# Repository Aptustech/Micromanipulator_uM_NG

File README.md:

# Micromanipulator_uM_NG

> ⚠️ **Disclaimer:** This is a preliminary hardware design and is currently **untested**. Use or produce these designs at your own risk.

**Micromanipulator_uM_NG** is a next-generation controller system designed for precision micromanipulation. It improves upon previous designs by introducing higher processing power, expanded I/O capabilities, reliable high-speed sensor communication, and comprehensive power monitoring.

## Acknowledgments & Prior Work

This project is the next-generation iteration of the original electronic system for [MicroManipulatorStepper](https://github.com/0x23/MicroManipulatorStepper) by [@0x23](https://github.com/0x23).
---

## Interactive KiCAD Design Viewers

You can inspect the schematics and PCB layouts directly in your browser without opening KiCAD, powered by [KiCanvas](https://kicanvas.org/):

* 🔗 **[View Sensor Board (MT6835 V1.0)](https://kicanvas.org/?repo=https%3A%2F%2Fgithub.com%2FAptustech%2FMicromanipulator_uM_NG%2Ftree%2Fmain%2FMT6835%2FV1.0%2FMT6835)**
* 🔗 **[View Controller Board (uM_Controller V1.0)](https://kicanvas.org/?repo=https%3A%2F%2Fgithub.com%2FAptustech%2FMicromanipulator_uM_NG%2Ftree%2Fmain%2FuM_Controller%2FV1.0%2FuM_Controller)**

---

## Key Features & Highlights

* **Powered by RP2350B:** Upgraded to the RP2350B microcontroller to leverage its high IO count and advanced processing capabilities.
* **High-Speed LVDS Link:** Uses Low-Voltage Differential Signaling (LVDS) lines between the main controller and sensor boards, enabling a high-speed, noise-resilient SPI bus operating at **15 MHz**.
* **Power & Diagnostics:**
  * **Input Voltage Monitoring:** Real-time tracking of the main supply voltage.
  * **Per-Motor Current Sensing:** Dedicated current monitoring for each individual motor driver channel.
* **Modular Expansion:** Includes an dedicated extension connector for easily adding custom interfaces, daughterboards, or peripheral modules.

---

## Hardware Repository Structure

```text
├── MT6835/
│   └── V1.0/          # MT6835 encoder/sensor board design files
└── uM_Controller/
    └── V1.0/          # Main RP2350B controller board design files

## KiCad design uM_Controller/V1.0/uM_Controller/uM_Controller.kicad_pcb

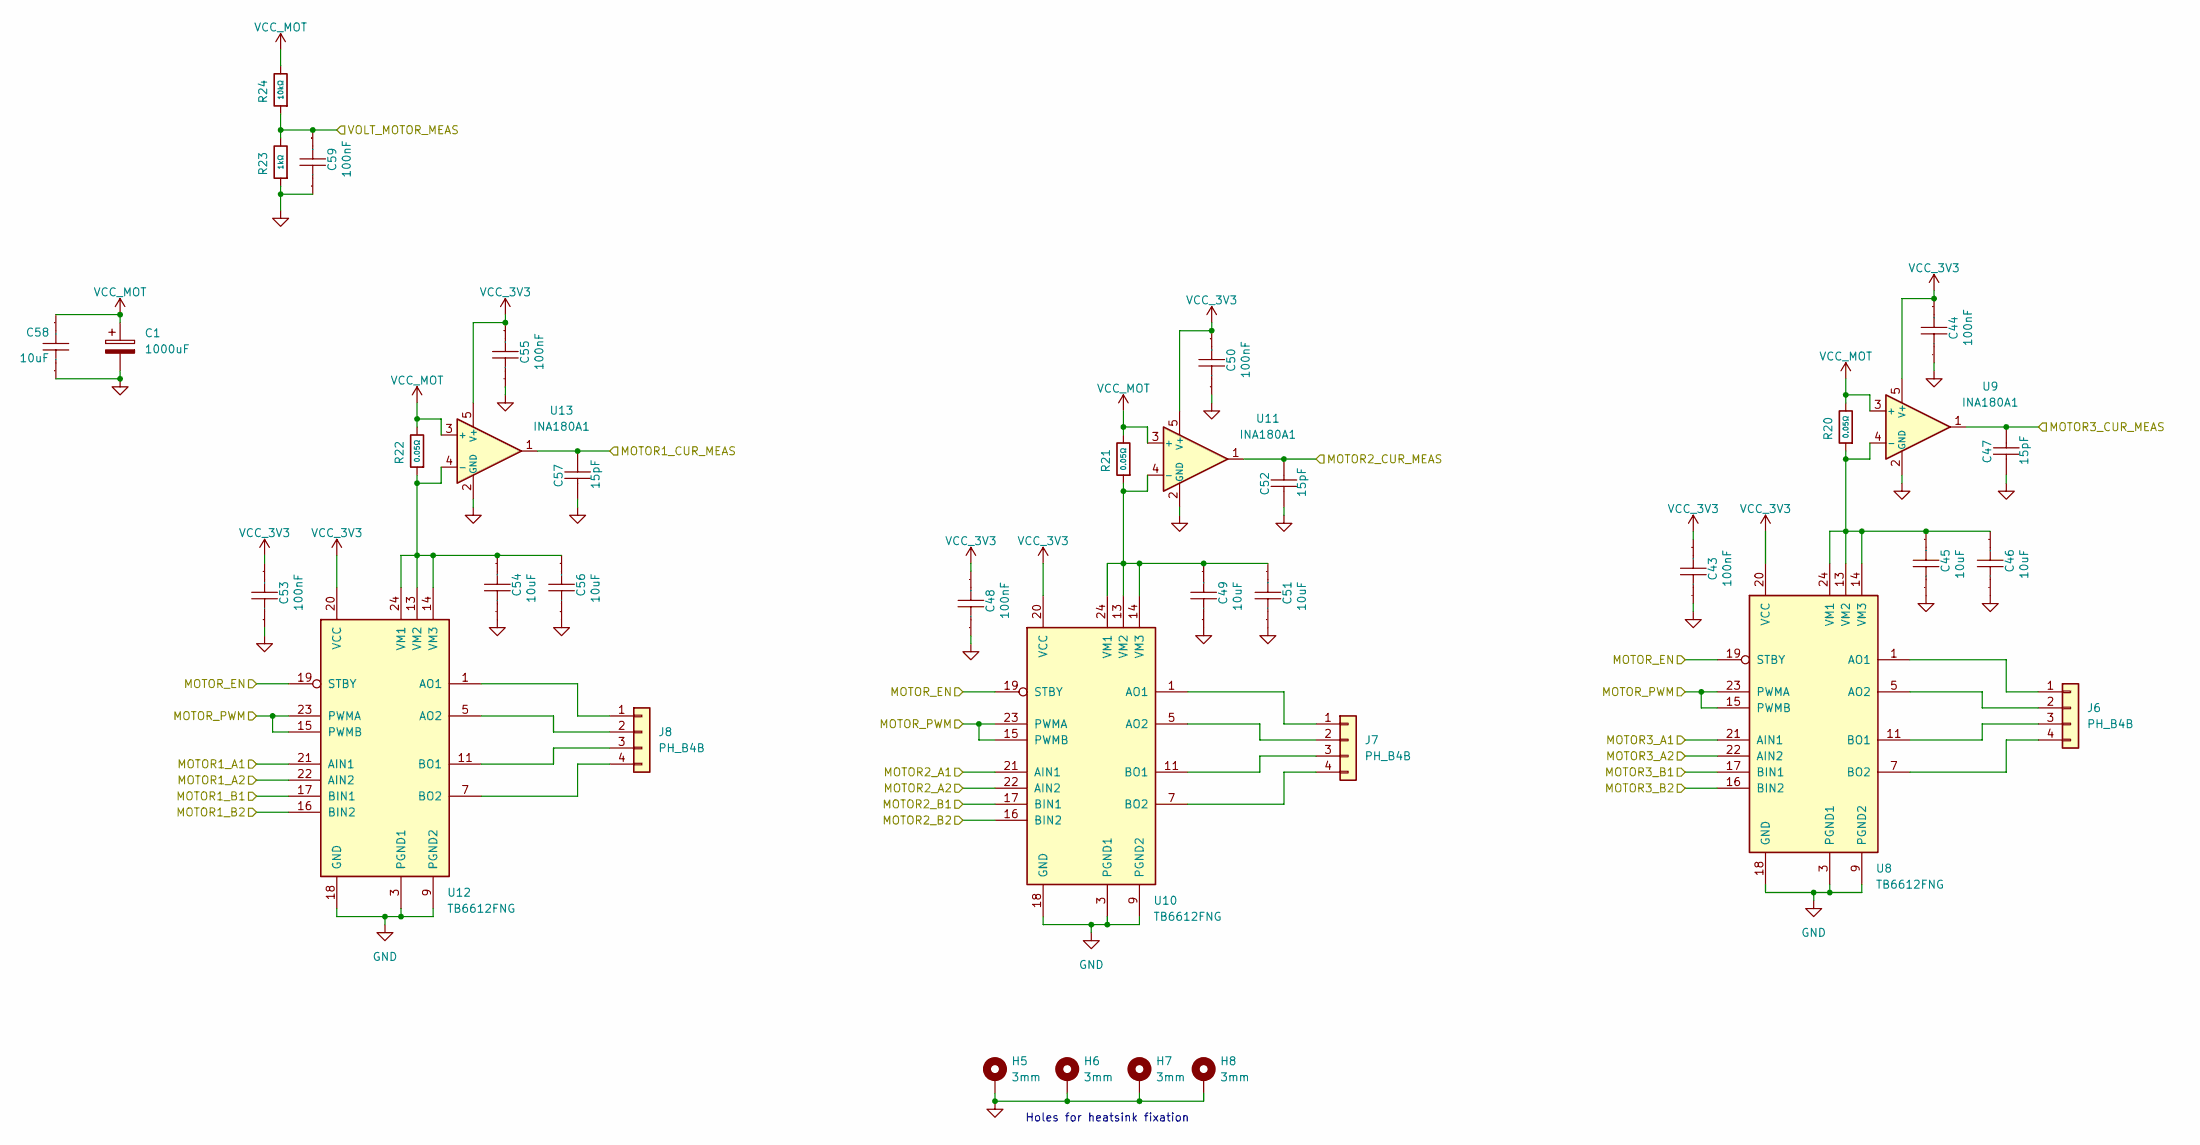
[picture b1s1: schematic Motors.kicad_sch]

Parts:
C1: 1000uF; CP_Radial_D10.0mm_P5.00mm_P7.50mm; Manufacturer Part 16ZLH1000MEFC10X16; LCSC C338175
C43, C44, C48, C50, C53, C55, C59: 100nF; C_0402_1005Metric; Manufacturer Part CL05B104KO5NNNC; LCSC Part Name 100nF ±10% 16V
C45, C46, C49, C51, C54, C56, C58: 10uF; C_1206_3216Metric; Manufacturer Part CL31A106KBHNNNE; LCSC Part Name 10uF ±10% 50V 1206
C47, C52, C57: 15pF; C_0402_1005Metric; Manufacturer Part 0402CG150J500NT; LCSC Part Name 15pF ±5% 50V
H5, H6, H7, H8: 3mm; MountingHole_3.2mm_M3_ISO14580_Pad_TopBottom
J6, J7, J8: PH_B4B; JST_PH_B4B-PH-K_1x04_P2.00mm_Vertical; Manufacturer Part PH-4A; LCSC C2321
R20, R21, R22: 0.05Ω; R_0805_2012Metric; Overload Voltage (Max) 50V; Tolerance ±1%; Part ERJ-6BWFR050V; LCSC C2075868
R23: 1kΩ; R_0402_1005Metric; Overload Voltage (Max) 50V; Tolerance ±1%; Part 0402WGF1001TCE; LCSC C11702
R24: 10kΩ; R_0402_1005Metric; Overload Voltage (Max) 50V; Tolerance ±1%; Part 0402WGF1002TCE; LCSC C25744
U8, U10, U12: TB6612FNG; SSOP-24_5.3x8.2mm_P0.65mm
U9, U11, U13: INA180A1; SOT-23-5

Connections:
/Motors/MOTOR1_A1: U12.21 (AIN1); also elsewhere on the board
/Motors/MOTOR1_A2: U12.22 (AIN2); also elsewhere on the board
/Motors/MOTOR1_B1: U12.17 (BIN1); also elsewhere on the board
/Motors/MOTOR1_B2: U12.16 (BIN2); also elsewhere on the board
/Motors/MOTOR1_CUR_MEAS: C57.1, U13.1; also elsewhere on the board
/Motors/MOTOR2_A1: U10.21 (AIN1); also elsewhere on the board
/Motors/MOTOR2_A2: U10.22 (AIN2); also elsewhere on the board
/Motors/MOTOR2_B1: U10.17 (BIN1); also elsewhere on the board
/Motors/MOTOR2_B2: U10.16 (BIN2); also elsewhere on the board
/Motors/MOTOR2_CUR_MEAS: C52.1, U11.1; also elsewhere on the board
/Motors/MOTOR3_A1: U8.21 (AIN1); also elsewhere on the board
/Motors/MOTOR3_A2: U8.22 (AIN2); also elsewhere on the board
/Motors/MOTOR3_B1: U8.17 (BIN1); also elsewhere on the board
/Motors/MOTOR3_B2: U8.16 (BIN2); also elsewhere on the board
/Motors/MOTOR3_CUR_MEAS: C47.1, U9.1; also elsewhere on the board
/Motors/MOTOR_EN: U8.19 (STBY), U10.19 (STBY), U12.19 (STBY); also elsewhere on the board
/Motors/MOTOR_PWM: U8.15 (PWMB), U8.23 (PWMA), U10.15 (PWMB), U10.23 (PWMA), U12.15 (PWMB), U12.23 (PWMA); also elsewhere on the board
/Motors/VOLT_MOTOR_MEAS: C59.1, R23.2, R24.1; also elsewhere on the board
GND: C1.2, C43.2, C44.2, C45.2, C46.2, C47.2, C48.2, C49.2, C50.2, C51.2, C52.2, C53.2, C54.2, C55.2, C56.2, C57.2, C58.2, C59.2, H5.1 (1_1), H6.1 (1_1), H7.1 (1_1), H8.1 (1_1), R23.1, U8.3 (PGND1), U8.4 (PGND1), U8.9 (PGND2), U8.10 (PGND2), U8.18 (GND), U9.2 (GND), U10.3 (PGND1), U10.4 (PGND1), U10.9 (PGND2), U10.10 (PGND2), U10.18 (GND), U11.2 (GND), U12.3 (PGND1), U12.4 (PGND1), U12.9 (PGND2), U12.10 (PGND2), U12.18 (GND), U13.2 (GND); also elsewhere on the board
unnamed: J6.1, U8.1 (AO1), U8.2 (AO1)
unnamed: J6.2, U8.5 (AO2), U8.6 (AO2)
unnamed: J6.3, U8.11 (BO1), U8.12 (BO1)
unnamed: J6.4, U8.7 (BO2), U8.8 (BO2)
unnamed: J7.1, U10.1 (AO1), U10.2 (AO1)
unnamed: J7.2, U10.5 (AO2), U10.6 (AO2)
unnamed: J7.3, U10.11 (BO1), U10.12 (BO1)
unnamed: J7.4, U10.7 (BO2), U10.8 (BO2)
unnamed: J8.1, U12.1 (AO1), U12.2 (AO1)
unnamed: J8.2, U12.5 (AO2), U12.6 (AO2)
unnamed: J8.3, U12.11 (BO1), U12.12 (BO1)
unnamed: J8.4, U12.7 (BO2), U12.8 (BO2)
unnamed: C45.1, C46.1, R20.1, U8.13 (VM2), U8.14 (VM3), U8.24 (VM1), U9.4 (-)
unnamed: C49.1, C51.1, R21.1, U10.13 (VM2), U10.14 (VM3), U10.24 (VM1), U11.4 (-)
unnamed: C54.1, C56.1, R22.1, U12.13 (VM2), U12.14 (VM3), U12.24 (VM1), U13.4 (-)
VCC_3V3: C43.1, C44.1, C48.1, C50.1, C53.1, C55.1, U8.20 (VCC), U9.5 (V+), U10.20 (VCC), U11.5 (V+), U12.20 (VCC), U13.5 (V+); also elsewhere on the board
VCC_MOT: C1.1, C58.1, R20.2, R21.2, R22.2, R24.2, U9.3 (+), U11.3 (+), U13.3 (+); also elsewhere on the board

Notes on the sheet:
Holes for heatsink fixation

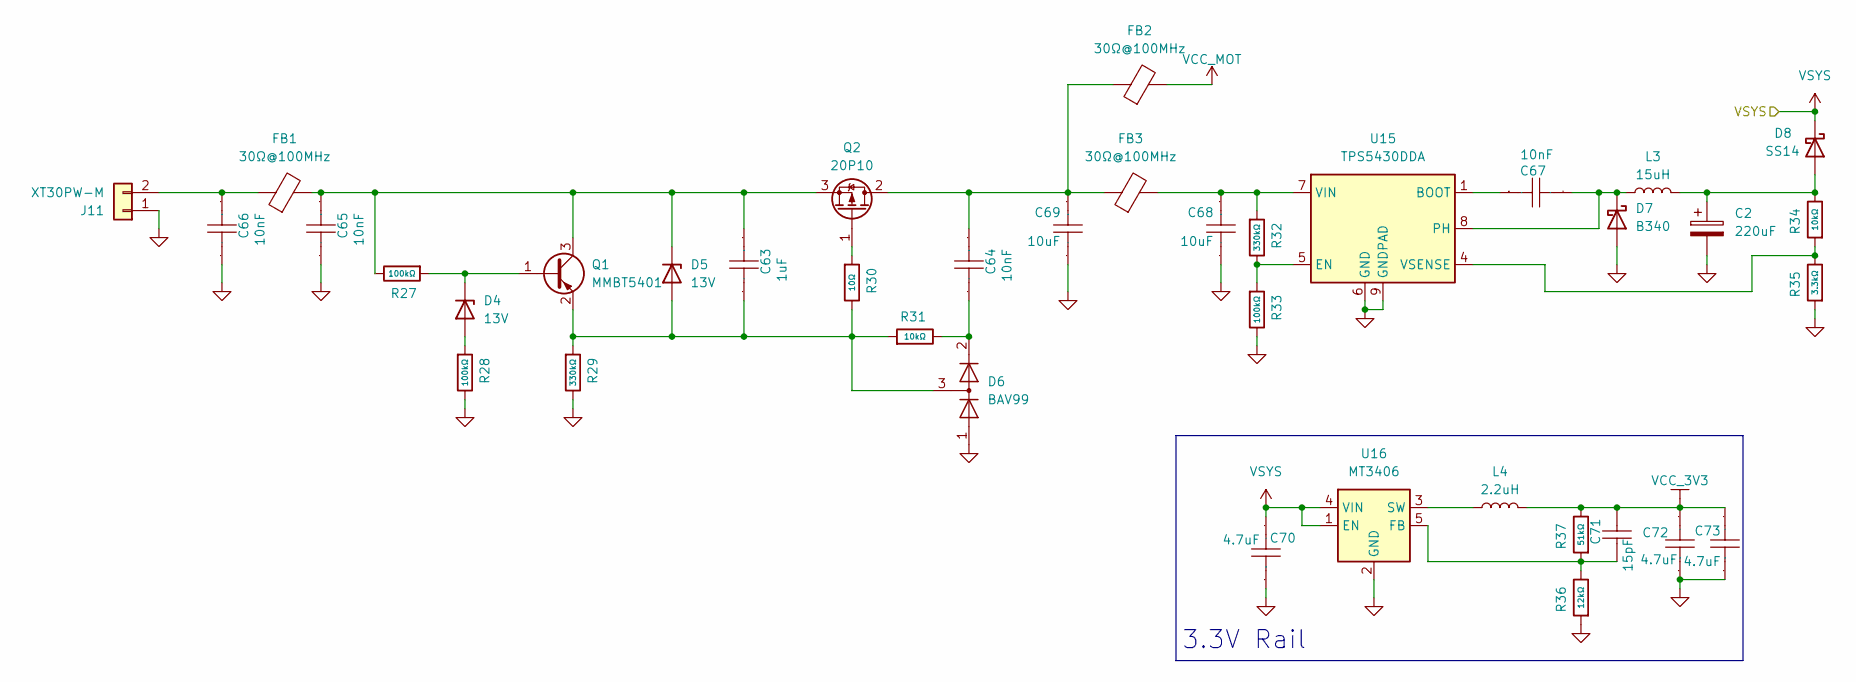
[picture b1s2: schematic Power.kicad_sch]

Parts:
C2: 220uF; CP_Radial_D6.3mm_P2.50mm; Manufacturer Part ERR1AM221E07OT; LCSC C105293
C63: 1uF; C_0603_1608Metric; Manufacturer Part CL10A105KB8NNNC; LCSC C15849
C64, C65, C66, C67: 10nF; C_0603_1608Metric; Manufacturer Part 0603B103K500NT; LCSC C57112
C68, C69: 10uF; C_1206_3216Metric; Manufacturer Part CL31A106KBHNNNE; LCSC Part Name 10uF ±10% 50V 1206
C70, C72, C73: 4.7uF; C_0402_1005Metric; Manufacturer Part CL05A475MP5NRNC; LCSC Part Name 4.7uF ±20% 10V
C71: 15pF; C_0402_1005Metric; Manufacturer Part 0402CG150J500NT; LCSC Part Name 15pF ±5% 50V
D4, D5: 13V; D_SOD-123; Manufacturer Part BZT52C13; LCSC BZT52C13
D6: BAV99; SOT-23; Manufacturer Part BAV99,215; LCSC C2500
D7: B340; D_SMC; Manufacturer Part B340-13-F-HXY; LCSC C52988714
D8: SS14; D_SMA; Manufacturer Part SS14; LCSC C2480
FB1, FB2, FB3: 30Ω@100MHz; L_0805_2012Metric; Manufacturer Part YI201209A300-10R0T; LCSC C20416195
J11: XT30PW-M; AMASS_XT30PW-M_1x02_P2.50mm_Horizontal
L3: 15uH; L_Taiyo-Yuden_NR-60xx; Manufacturer Part FNR6045S150MT; LCSC C168078
L4: 2.2uH; L_1008_2520Metric; Manufacturer Part FTC252010S2R2MBCA; LCSC C5832358
Q1: MMBT5401; SOT-23; Manufacturer Part MMBT5401(RANGE:200-300); LCSC C8326
Q2: 20P10; TO-252-2; Manufacturer Part 20P10; LCSC C18164396
R27, R28, R33: 100kΩ; R_0603_1608Metric; Overload Voltage (Max) 75V; Tolerance ±1%; Part 0603WAF1003T5E; LCSC C25803
R29, R32: 330kΩ; R_0603_1608Metric; Overload Voltage (Max) 75V; Tolerance ±1%; Part 0603WAF3303T5E; LCSC C23137
R30: 10Ω; R_0603_1608Metric; Overload Voltage (Max) 75V; Tolerance ±1%; Part 0603WAF100JT5E; LCSC C22859
R31: 10kΩ; R_0603_1608Metric; Overload Voltage (Max) 75V; Tolerance ±1%; Part 0603WAF1002T5E; LCSC C25804
R34: 10kΩ; R_0402_1005Metric; Overload Voltage (Max) 50V; Tolerance ±1%; Part 0402WGF1002TCE; LCSC C25744
R35: 3.3kΩ; R_0402_1005Metric; Overload Voltage (Max) 50V; Tolerance ±1%; Part 0402WGF3301TCE; LCSC C25890
R36: 12kΩ; R_0402_1005Metric; Overload Voltage (Max) 50V; Tolerance ±1%; Part 0402WGF1202TCE; LCSC C25752
R37: 51kΩ; R_0402_1005Metric; Overload Voltage (Max) 50V; Tolerance ±1%; Part 0402WGF5102TCE; LCSC C25794
U15: TPS5430DDA; TI_SO-PowerPAD-8_ThermalVias; Manufacturer Part TPS5430DDA; LCSC C9864
U16: MT3406; SOT-23-5; Manufacturer Part MT3406; LCSC C22462728

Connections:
GND: C2.2, C65.2, C66.2, C68.2, C69.2, C70.1, C72.1, C73.1, D6.1 (K), D7.2 (A), J11.1, R28.2, R29.2, R33.2, R35.1, R36.1, U15.6 (GND), U15.9 (GNDPAD), U16.2 (GND); also elsewhere on the board
unnamed: D4.2 (A), R28.1
unnamed: D4.1 (K), Q1.1 (B), R27.1
unnamed: C63.2, D5.2 (A), D6.3 (K), Q1.2 (E), R29.1, R30.2, R31.1
unnamed: C63.1, C65.1, D5.1 (K), FB1.2, Q1.3 (C), Q2.3 (S), R27.2
unnamed: C64.2, D6.2 (A), R31.2
unnamed: C67.2, D7.1 (K), L3.1, U15.8 (PH)
unnamed: C2.1, D8.2 (A), L3.2, R34.2
unnamed: C66.1, FB1.1, J11.2
unnamed: C64.1, C69.1, FB2.1, FB3.1, Q2.2 (D)
unnamed: Q2.1 (G), R30.1
unnamed: C67.1, U15.1 (BOOT)
unnamed: R32.2, R33.1, U15.5 (EN)
unnamed: C68.1, FB3.2, R32.1, U15.7 (VIN)
unnamed: R34.1, R35.2, U15.4 (VSENSE)
unnamed: C71.2, R36.2, R37.1, U16.5 (FB)
unnamed: L4.1, U16.3 (SW)
VCC_3V3: C71.1, C72.2, C73.2, L4.2, R37.2; also elsewhere on the board
VCC_MOT: FB2.2; also elsewhere on the board
VSYS: C70.2, D8.1 (K), U16.1 (EN), U16.4 (VIN); also elsewhere on the board

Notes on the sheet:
3.3V Rail

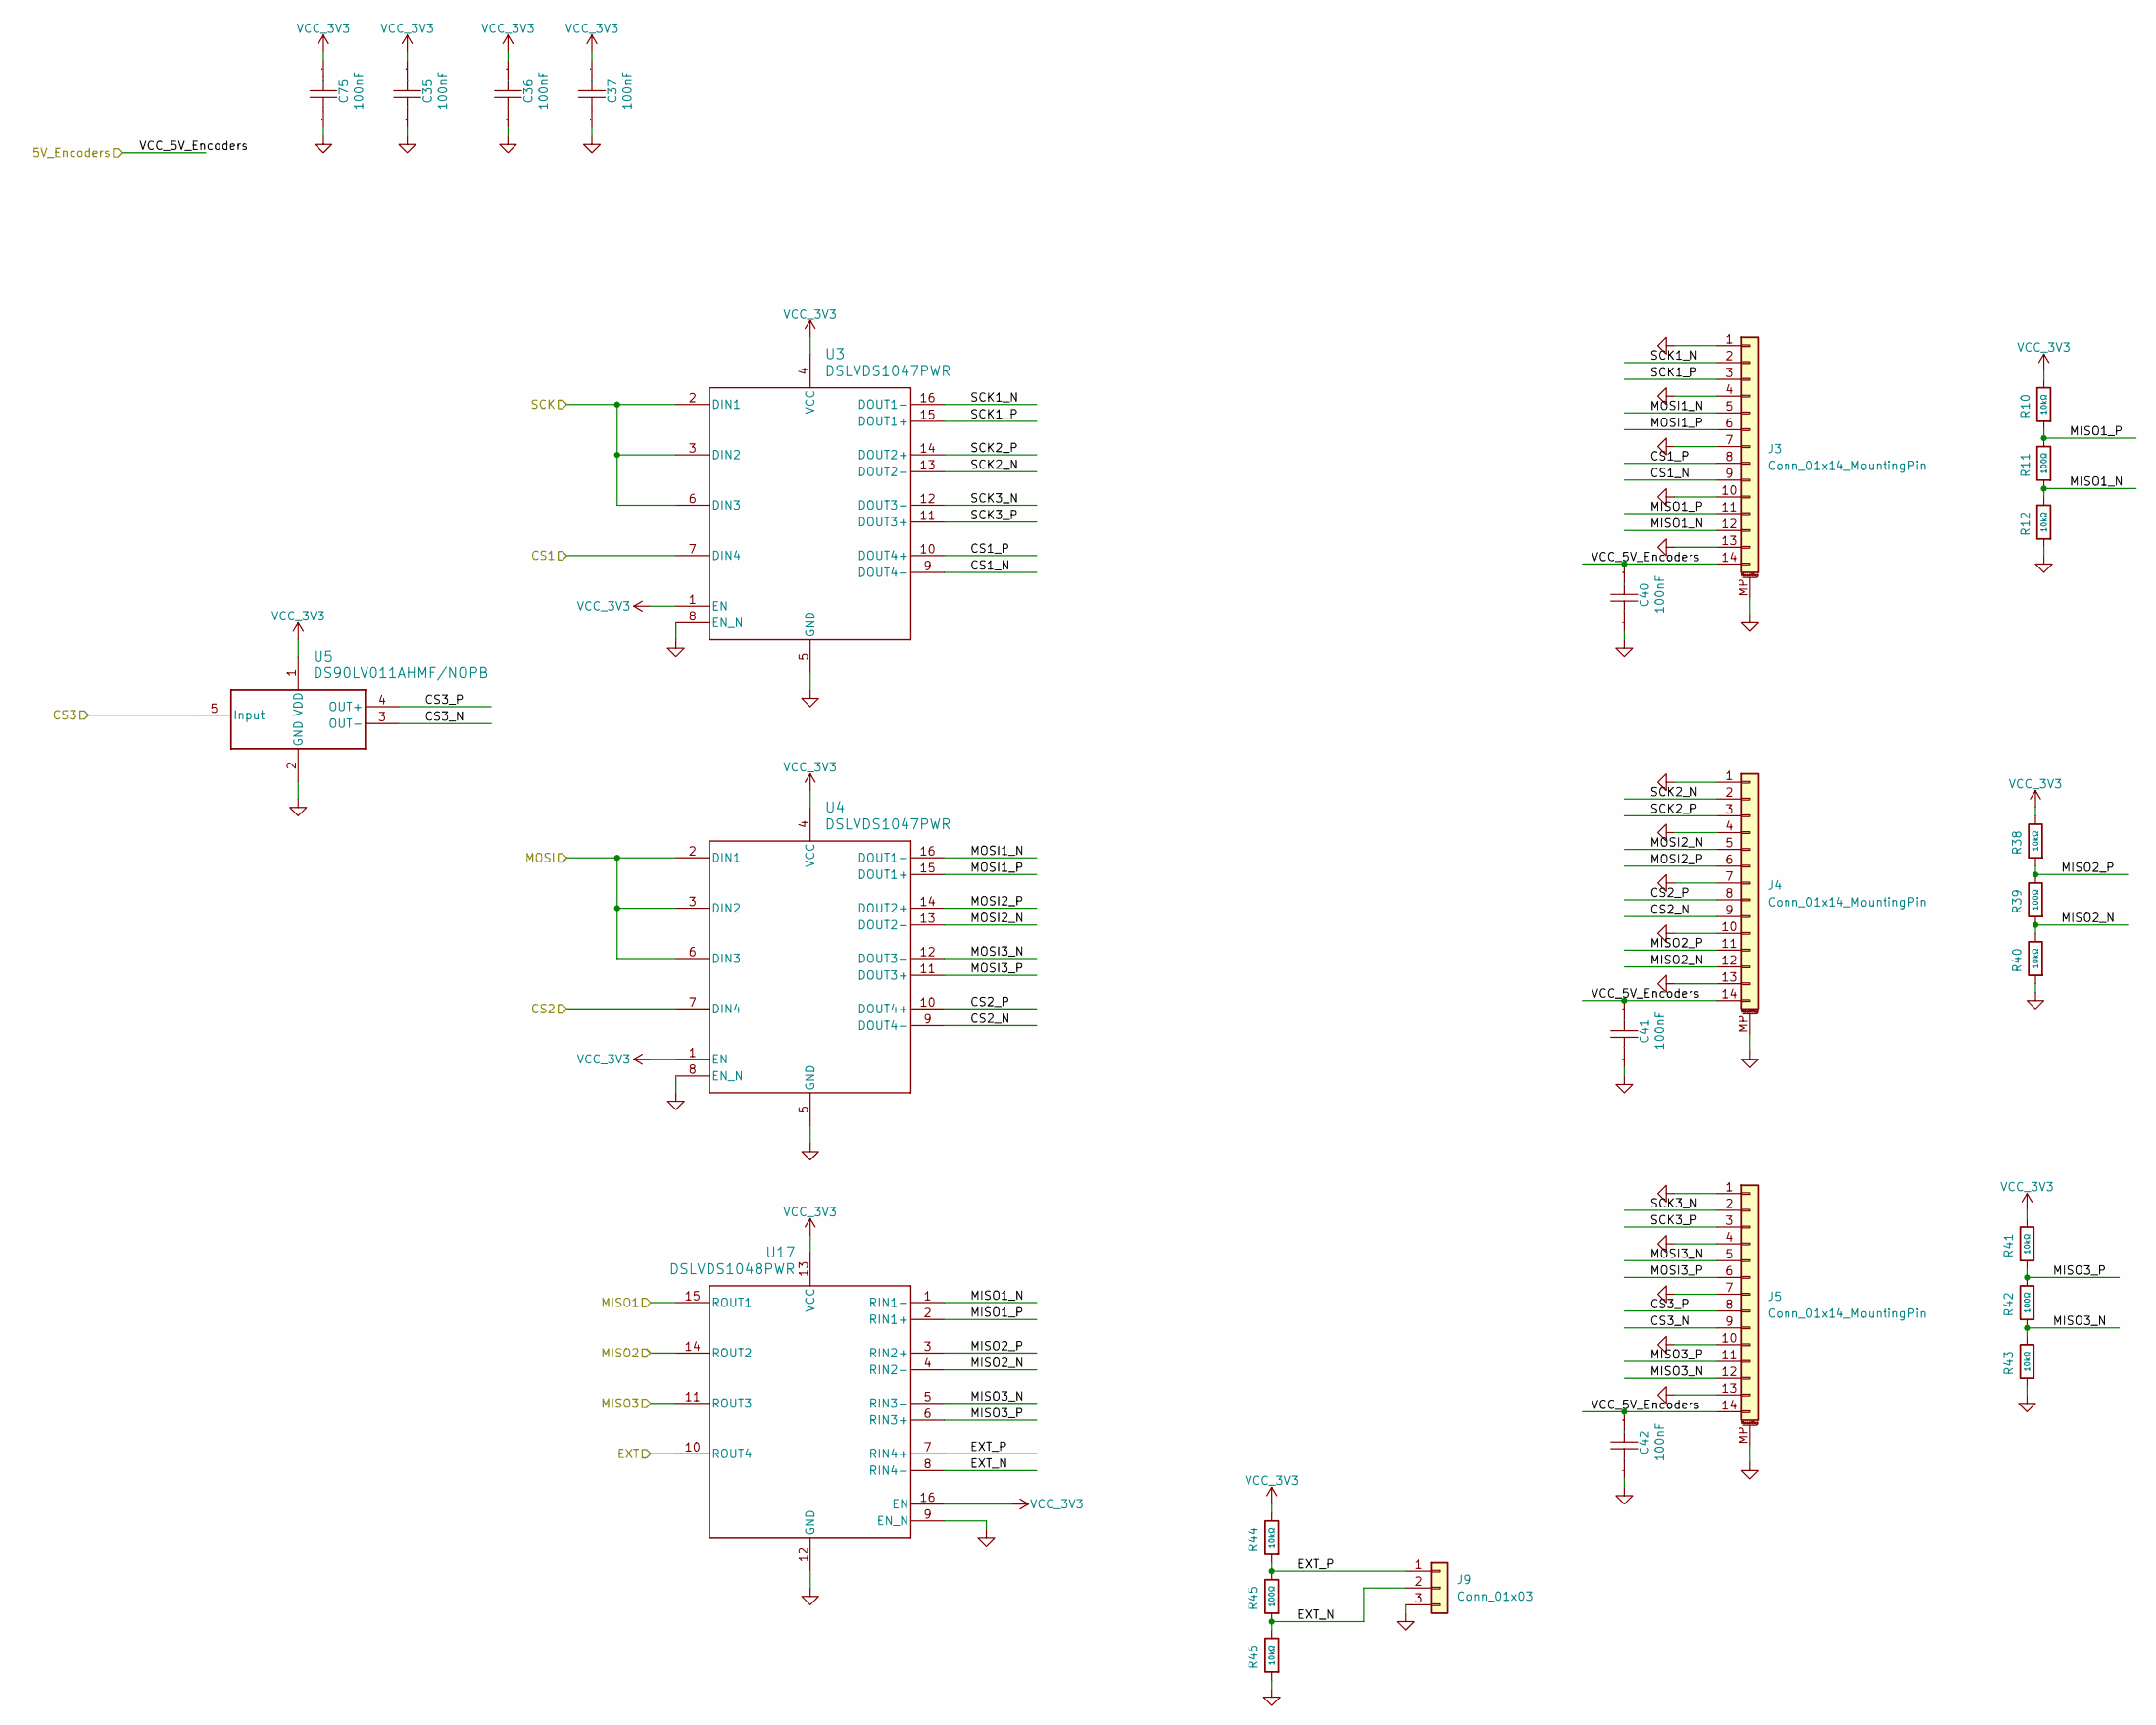
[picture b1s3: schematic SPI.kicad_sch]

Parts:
C35, C36, C37, C40, C41, C42, C75: 100nF; C_0402_1005Metric; Manufacturer Part CL05B104KO5NNNC; LCSC Part Name 100nF ±10% 16V
J3, J4, J5: Conn_01x14_MountingPin; Amphenol_F32R-1A7x1-11014_1x14-1MP_P0.5mm_Horizontal; Manufacturer Part F32R-1A7H1-11014 / AFC07-S14FCC-00; LCSC C38179
J9: Conn_01x03; PinHeader_1x03_P2.54mm_Vertical
R10, R12, R38, R40, R41, R43, R44, R46: 10kΩ; R_0402_1005Metric; Overload Voltage (Max) 50V; Tolerance ±1%; Part 0402WGF1002TCE; LCSC C25744
R11, R39, R42, R45: 100Ω; R_0402_1005Metric; Overload Voltage (Max) 50V; Tolerance ±1%; Part 0402WGF1000TCE; LCSC C25076
U3, U4: DSLVDS1047PWR; TSSOP-16_4.4x5mm_P0.65mm; Manufacturer Part DSLVDS1047PWR; LCSC C2671205
U5: DS90LV011AHMF/NOPB; SOT-23-5; Manufacturer Part DS90LV011AHMF/NOPB; LCSC C2671548
U17: DSLVDS1048PWR; TSSOP-16_4.4x5mm_P0.65mm; Manufacturer Part DSLVDS1048PWR; LCSC C2671655

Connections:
/RP2350B/CS1: U3.7 (DIN4); also elsewhere on the board
/RP2350B/CS2: U4.7 (DIN4); also elsewhere on the board
/RP2350B/CS3: U5.5 (Input); also elsewhere on the board
/RP2350B/MISO1: U17.15 (ROUT1); also elsewhere on the board
/RP2350B/MISO2: U17.14 (ROUT2); also elsewhere on the board
/RP2350B/MISO3: U17.11 (ROUT3); also elsewhere on the board
/RP2350B/SPI0_MOSI: U4.2 (DIN1), U4.3 (DIN2), U4.6 (DIN3); also elsewhere on the board
/RP2350B/SPI0_SCK: U3.2 (DIN1), U3.3 (DIN2), U3.6 (DIN3); also elsewhere on the board
/SPI_Encoders/CS1_N: J3.9, U3.9 (DOUT4-)
/SPI_Encoders/CS1_P: J3.8, U3.10 (DOUT4+)
/SPI_Encoders/CS2_N: J4.9, U4.9 (DOUT4-)
/SPI_Encoders/CS2_P: J4.8, U4.10 (DOUT4+)
/SPI_Encoders/CS3_N: J5.9, U5.3 (OUT-)
/SPI_Encoders/CS3_P: J5.8, U5.4 (OUT+)
/SPI_Encoders/EXT: U17.10 (ROUT4)
/SPI_Encoders/EXT_N: J9.2, R45.1, R46.2, U17.8 (RIN4-)
/SPI_Encoders/EXT_P: J9.1, R44.1, R45.2, U17.7 (RIN4+)
/SPI_Encoders/MISO1_N: J3.12, R11.1, R12.2, U17.1 (RIN1-)
/SPI_Encoders/MISO1_P: J3.11, R10.1, R11.2, U17.2 (RIN1+)
/SPI_Encoders/MISO2_N: J4.12, R39.1, R40.2, U17.4 (RIN2-)
/SPI_Encoders/MISO2_P: J4.11, R38.1, R39.2, U17.3 (RIN2+)
/SPI_Encoders/MISO3_N: J5.12, R42.1, R43.2, U17.5 (RIN3-)
/SPI_Encoders/MISO3_P: J5.11, R41.1, R42.2, U17.6 (RIN3+)
/SPI_Encoders/MOSI1_N: J3.5, U4.16 (DOUT1-)
/SPI_Encoders/MOSI1_P: J3.6, U4.15 (DOUT1+)
/SPI_Encoders/MOSI2_N: J4.5, U4.13 (DOUT2-)
/SPI_Encoders/MOSI2_P: J4.6, U4.14 (DOUT2+)
/SPI_Encoders/MOSI3_N: J5.5, U4.12 (DOUT3-)
/SPI_Encoders/MOSI3_P: J5.6, U4.11 (DOUT3+)
/SPI_Encoders/SCK1_N: J3.2, U3.16 (DOUT1-)
/SPI_Encoders/SCK1_P: J3.3, U3.15 (DOUT1+)
/SPI_Encoders/SCK2_N: J4.2, U3.13 (DOUT2-)
/SPI_Encoders/SCK2_P: J4.3, U3.14 (DOUT2+)
/SPI_Encoders/SCK3_N: J5.2, U3.12 (DOUT3-)
/SPI_Encoders/SCK3_P: J5.3, U3.11 (DOUT3+)
/SPI_Encoders/VCC_5V_Encoders: C40.1, C41.1, C42.1, J3.14, J4.14, J5.14; also elsewhere on the board
GND: C35.2, C36.2, C37.2, C40.2, C41.2, C42.2, C75.2, J3.1, J3.4, J3.7, J3.10, J3.13, J3.MP (MountPin), J4.1, J4.4, J4.7, J4.10, J4.13, J4.MP (MountPin), J5.1, J5.4, J5.7, J5.10, J5.13, J5.MP (MountPin), J9.3, R12.1, R40.1, R43.1, R46.1, U3.5 (GND), U3.8 (EN_N), U4.5 (GND), U4.8 (EN_N), U5.2 (GND), U17.9 (EN_N), U17.12 (GND); also elsewhere on the board
VCC_3V3: C35.1, C36.1, C37.1, C75.1, R10.2, R38.2, R41.2, R44.2, U3.1 (EN), U3.4 (VCC), U4.1 (EN), U4.4 (VCC), U5.1 (VDD), U17.13 (VCC), U17.16 (EN); also elsewhere on the board
